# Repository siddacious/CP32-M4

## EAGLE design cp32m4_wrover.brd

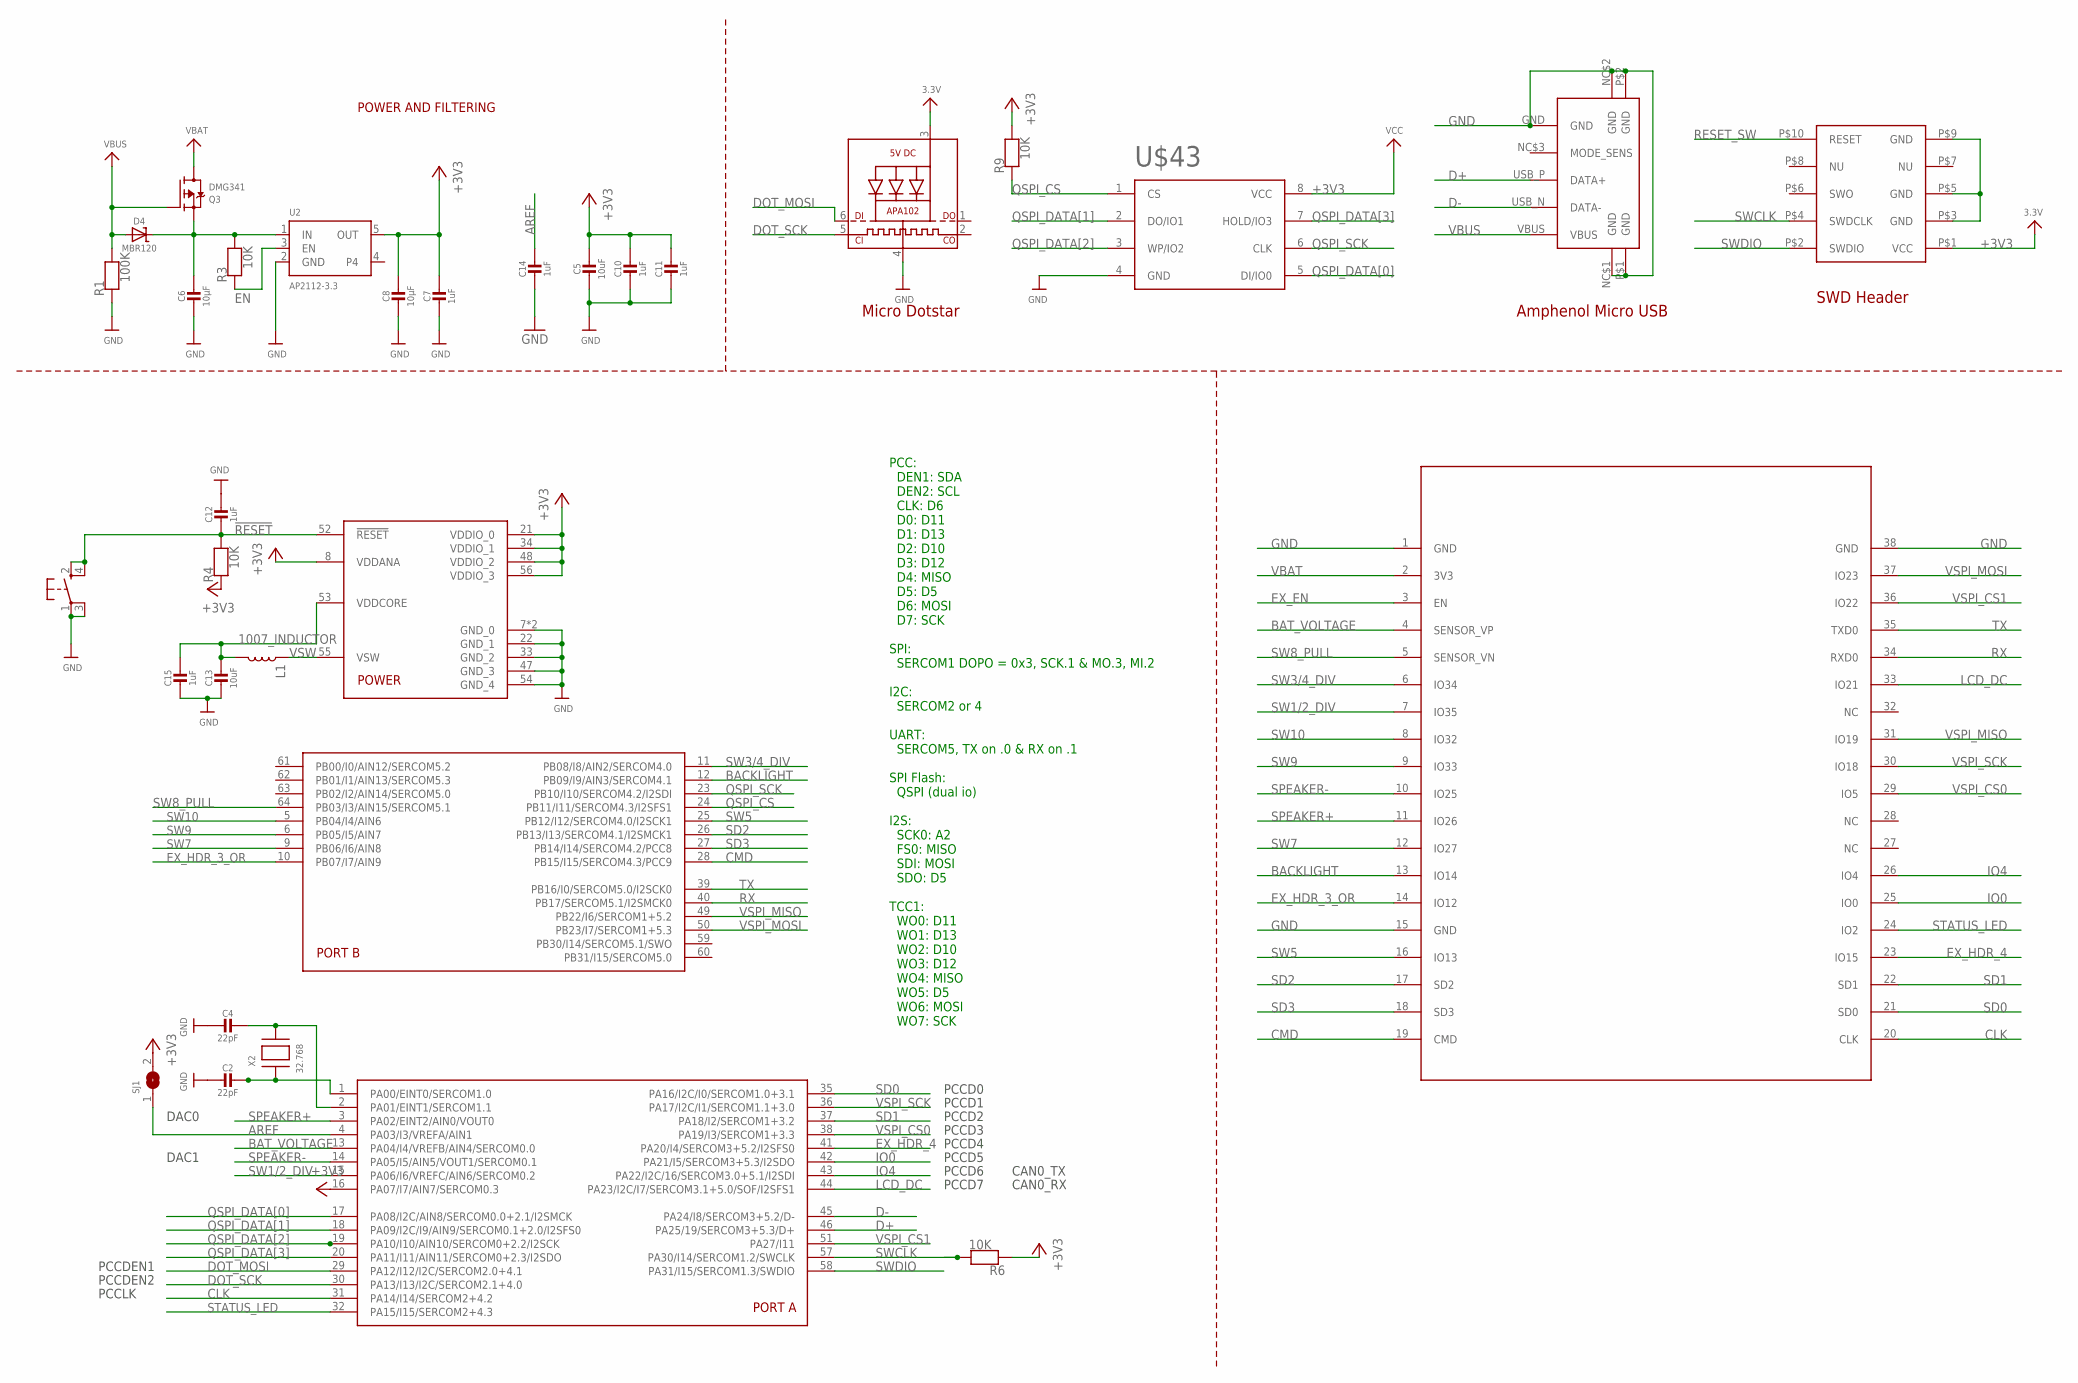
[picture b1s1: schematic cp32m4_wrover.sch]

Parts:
C2, C4: 22pF; 0603-NO
C5, C13: 10uF; 0805-NO
C6, C8: 10µF; 0805-NO
C7, C10, C11, C12, C14, C15: 1uF; 0603-NO
D4: MBR120; SOD-123
L1: 1007_INDUCTOR
LED2: AP102-2020; APA102_2020
Q3: DMG341; SOT23-R
R1: 100K; 0603-NO
R3, R4, R6, R9: 10K; 0603-NO
SJ1: SOLDERJUMPERCLOSED; SOLDERJUMPER_CLOSEDWIRE
SW1: SPST_TACT-KMR2; KMR2
U2: AP2112-3.3; SOT23-5
U$7: ESP32_WROVER
U$14: ATSAMD51J; PQFN64-1
U$43: WINDBOND_QSPI_FLASHWSON_6X5; WSON_6X5MM
U$44: SWD_HEADER; AMPHENOL_SWD
U$50: AMPHENOL_MICRO_USBAMPHENOL_MICRO_USB_BETTER; BETTER_AMP_MICRO_USB
X2: 32.768; XTAL3215

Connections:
!RESET: C12.2, R4.2, SW1.2 (S), SW1.4 (S1), U$14.52 (!RESET)
+3V3: C5.1, C7.1, C8.1, C10.1, C11.1, LED2.3 (VDD), R4.1, R6.1, R9.2, SJ1.2, U2.5 (OUT), U$14.8 (VDDANA), U$14.16 (PA07/I7/AIN7/SERCOM0.3), U$14.21 (VDDIO_0), U$14.34 (VDDIO_1), U$14.48 (VDDIO_2), U$14.56 (VDDIO_3), U$43.8 (VCC), U$44.P$1 (VCC)
AREF: C14.1, SJ1.1, U$14.4 (PA03/I3/VREFA/AIN1)
BACKLIGHT: U$7.13 (IO14), U$14.12 (PB09/I9/AIN3/SERCOM4.1)
BAT_VOLTAGE: U$7.4 (SENSOR_VP), U$14.13 (PA04/I4/VREFB/AIN4/SERCOM0.0)
CLK: U$7.20 (CLK), U$14.31 (PA14/I14/SERCOM2+4.2)
CMD: U$7.19 (CMD), U$14.28 (PB15/I15/SERCOM4.3/PCC9)
D+: U$14.46 (PA25/19/SERCOM3+5.3/D+), U$50.USB_P (DATA+)
D-: U$14.45 (PA24/I8/SERCOM3+5.2/D-), U$50.USB_N (DATA-)
DOT_MOSI: LED2.6 (DI), U$14.29 (PA12/I12/I2C/SERCOM2.0+4.1)
DOT_SCK: LED2.5 (CKI), U$14.30 (PA13/I13/I2C/SERCOM2.1+4.0)
EN: R3.1, U2.3 (EN)
EX_EN: U$7.3 (EN)
EX_HDR_3_OR: U$7.14 (IO12), U$14.10 (PB07/I7/AIN9)
EX_HDR_4: U$7.23 (IO15), U$14.41 (PA20/I4/SERCOM3+5.2/I2SFS0)
GND: C2.2, C4.2, C5.2, C6.2, C7.2, C8.2, C10.2, C11.2, C12.1, C13.2, C14.2, C15.2, LED2.4 (GND), R1.1, SW1.1, SW1.3 (P1), U2.2 (GND), U$7.1 (GND), U$7.15 (GND), U$7.38 (GND), U$14.7 (GND_0), U$14.22 (GND_1), U$14.33 (GND_2), U$14.47 (GND_3), U$14.54 (GND_4), U$14.EXP (GND_0), U$43.4 (GND), U$44.P$3 (GND), U$44.P$5 (GND), U$44.P$9 (GND), U$50.GND, U$50.NC$1 (GND), U$50.NC$2 (GND), U$50.P$1 (GND), U$50.P$2 (GND)
IO0: U$7.25 (IO0), U$14.42 (PA21/I5/SERCOM3+5.3/I2SDO)
IO4: U$7.26 (IO4), U$14.43 (PA22/I2C/16/SERCOM3.0+5.1/I2SDI)
LCD_DC: U$7.33 (IO21), U$14.44 (PA23/I2C/I7/SERCOM3.1+5.0/SOF/I2SFS1)
unnamed: C2.1, U$14.1 (PA00/EINT0/SERCOM1.0), X2.P$1
unnamed: C4.1, U$14.2 (PA01/EINT1/SERCOM1.1), X2.P$2
QSPI_CS: R9.1, U$14.24 (PB11/I11/SERCOM4.3/I2SFS1), U$43.1 (CS)
QSPI_DATA[0]: U$14.17 (PA08/I2C/AIN8/SERCOM0.0+2.1/I2SMCK), U$43.5 (DI/IO0)
QSPI_DATA[1]: U$14.18 (PA09/I2C/I9/AIN9/SERCOM0.1+2.0/I2SFS0), U$43.2 (DO/IO1)
QSPI_DATA[2]: U$14.19 (PA10/I10/AIN10/SERCOM0+2.2/I2SCK), U$43.3 (WP/IO2)
QSPI_DATA[3]: U$14.20 (PA11/I11/AIN11/SERCOM0+2.3/I2SDO), U$43.7 (HOLD/IO3)
QSPI_SCK: U$14.23 (PB10/I10/SERCOM4.2/I2SDI), U$43.6 (CLK)
RESET_SW: U$44.P$10 (RESET)
RX: U$7.34 (RXD0), U$14.40 (PB17/SERCOM5.1/I2SMCK0)
SD0: U$7.21 (SD0), U$14.35 (PA16/I2C/I0/SERCOM1.0+3.1)
SD1: U$7.22 (SD1), U$14.37 (PA18/I2/SERCOM1+3.2)
SD2: U$7.17 (SD2), U$14.26 (PB13/I13/SERCOM4.1/I2SMCK1)
SD3: U$7.18 (SD3), U$14.27 (PB14/I14/SERCOM4.2/PCC8)
SPEAKER+: U$7.11 (IO26), U$14.3 (PA02/EINT2/AIN0/VOUT0)
SPEAKER-: U$7.10 (IO25), U$14.14 (PA05/I5/AIN5/VOUT1/SERCOM0.1)
STATUS_LED: U$7.24 (IO2), U$14.32 (PA15/I15/SERCOM2+4.3)
SW1/2_DIV: U$7.7 (IO35), U$14.15 (PA06/I6/VREFC/AIN6/SERCOM0.2)
SW3/4_DIV: U$7.6 (IO34), U$14.11 (PB08/I8/AIN2/SERCOM4.0)
SW5: U$7.16 (IO13), U$14.25 (PB12/I12/SERCOM4.0/I2SCK1)
SW7: U$7.12 (IO27), U$14.9 (PB06/I6/AIN8)
SW8_PULL: U$7.5 (SENSOR_VN), U$14.64 (PB03/I3/AIN15/SERCOM5.1)
SW9: U$7.9 (IO33), U$14.6 (PB05/I5/AIN7)
SW10: U$7.8 (IO32), U$14.5 (PB04/I4/AIN6)
SWCLK: R6.2, U$14.57 (PA30/I14/SERCOM1.2/SWCLK), U$44.P$4 (SWDCLK)
SWDIO: U$14.58 (PA31/I15/SERCOM1.3/SWDIO), U$44.P$2 (SWDIO)
TX: U$7.35 (TXD0), U$14.39 (PB16/I0/SERCOM5.0/I2SCK0)
VBAT: Q3.3 (D), U$7.2 (3V3)
VBUS: D4.A, Q3.1 (G), R1.2, U$50.VBUS
VDDCORE1: C13.1, C15.1, L1.P$2 (2), U$14.53 (VDDCORE)
VHI: C6.1, D4.C, Q3.2 (S), R3.2, U2.1 (IN)
VSPI_CS0: U$7.29 (IO5), U$14.38 (PA19/I3/SERCOM1+3.3)
VSPI_CS1: U$7.36 (IO22), U$14.51 (PA27/I11)
VSPI_MISO: U$7.31 (IO19), U$14.49 (PB22/I6/SERCOM1+5.2)
VSPI_MOSI: U$7.37 (IO23), U$14.50 (PB23/I7/SERCOM1+5.3)
VSPI_SCK: U$7.30 (IO18), U$14.36 (PA17/I2C/I1/SERCOM1.1+3.0)
VSW: L1.P$1 (1), U$14.55 (VSW)

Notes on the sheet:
POWER AND FILTERING
PCCDEN1
PCCDEN2
PCCD0
PCCD1
PCCD2
PCCD3
PCCD4
PCCD5
PCCD6
PCCD7
PCCLK
PCC: DEN1: SDA DEN2: SCL CLK: D6 D0: D11 D1: D13 D2: D10 D3: D12 D4: MISO D5: D5 D6: MOSI D7: SCK SPI: SERCOM1 DOPO = 0x3, SCK.1 & MO.3, MI.2 I2C: SERCOM2 or 4 UART: SERCOM5, TX on .0 & RX on .1 SPI Flash: QSPI (dual io) I2S: SCK0: A2 FS0: MISO SDI: MOSI SDO: D5 TCC1: WO0: D11 WO1: D13 WO2: D10 WO3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
CAN0_TX
CAN0_RX
DAC0
DAC1
SWD Header
Micro Dotstar
Amphenol Micro USB

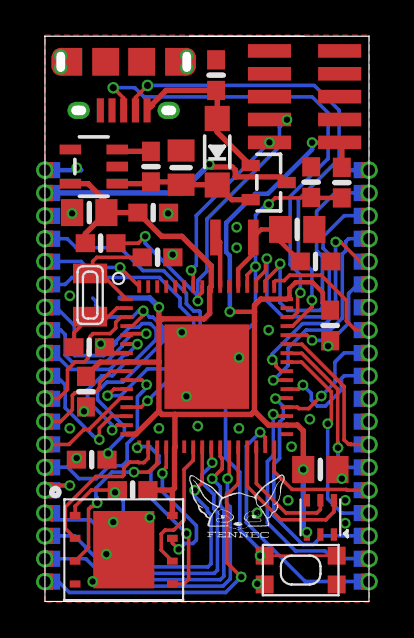
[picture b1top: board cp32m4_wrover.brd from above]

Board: 2 copper layers, 17.5 x 30.9 mm, 30 parts (1 on the bottom side), 54 nets.

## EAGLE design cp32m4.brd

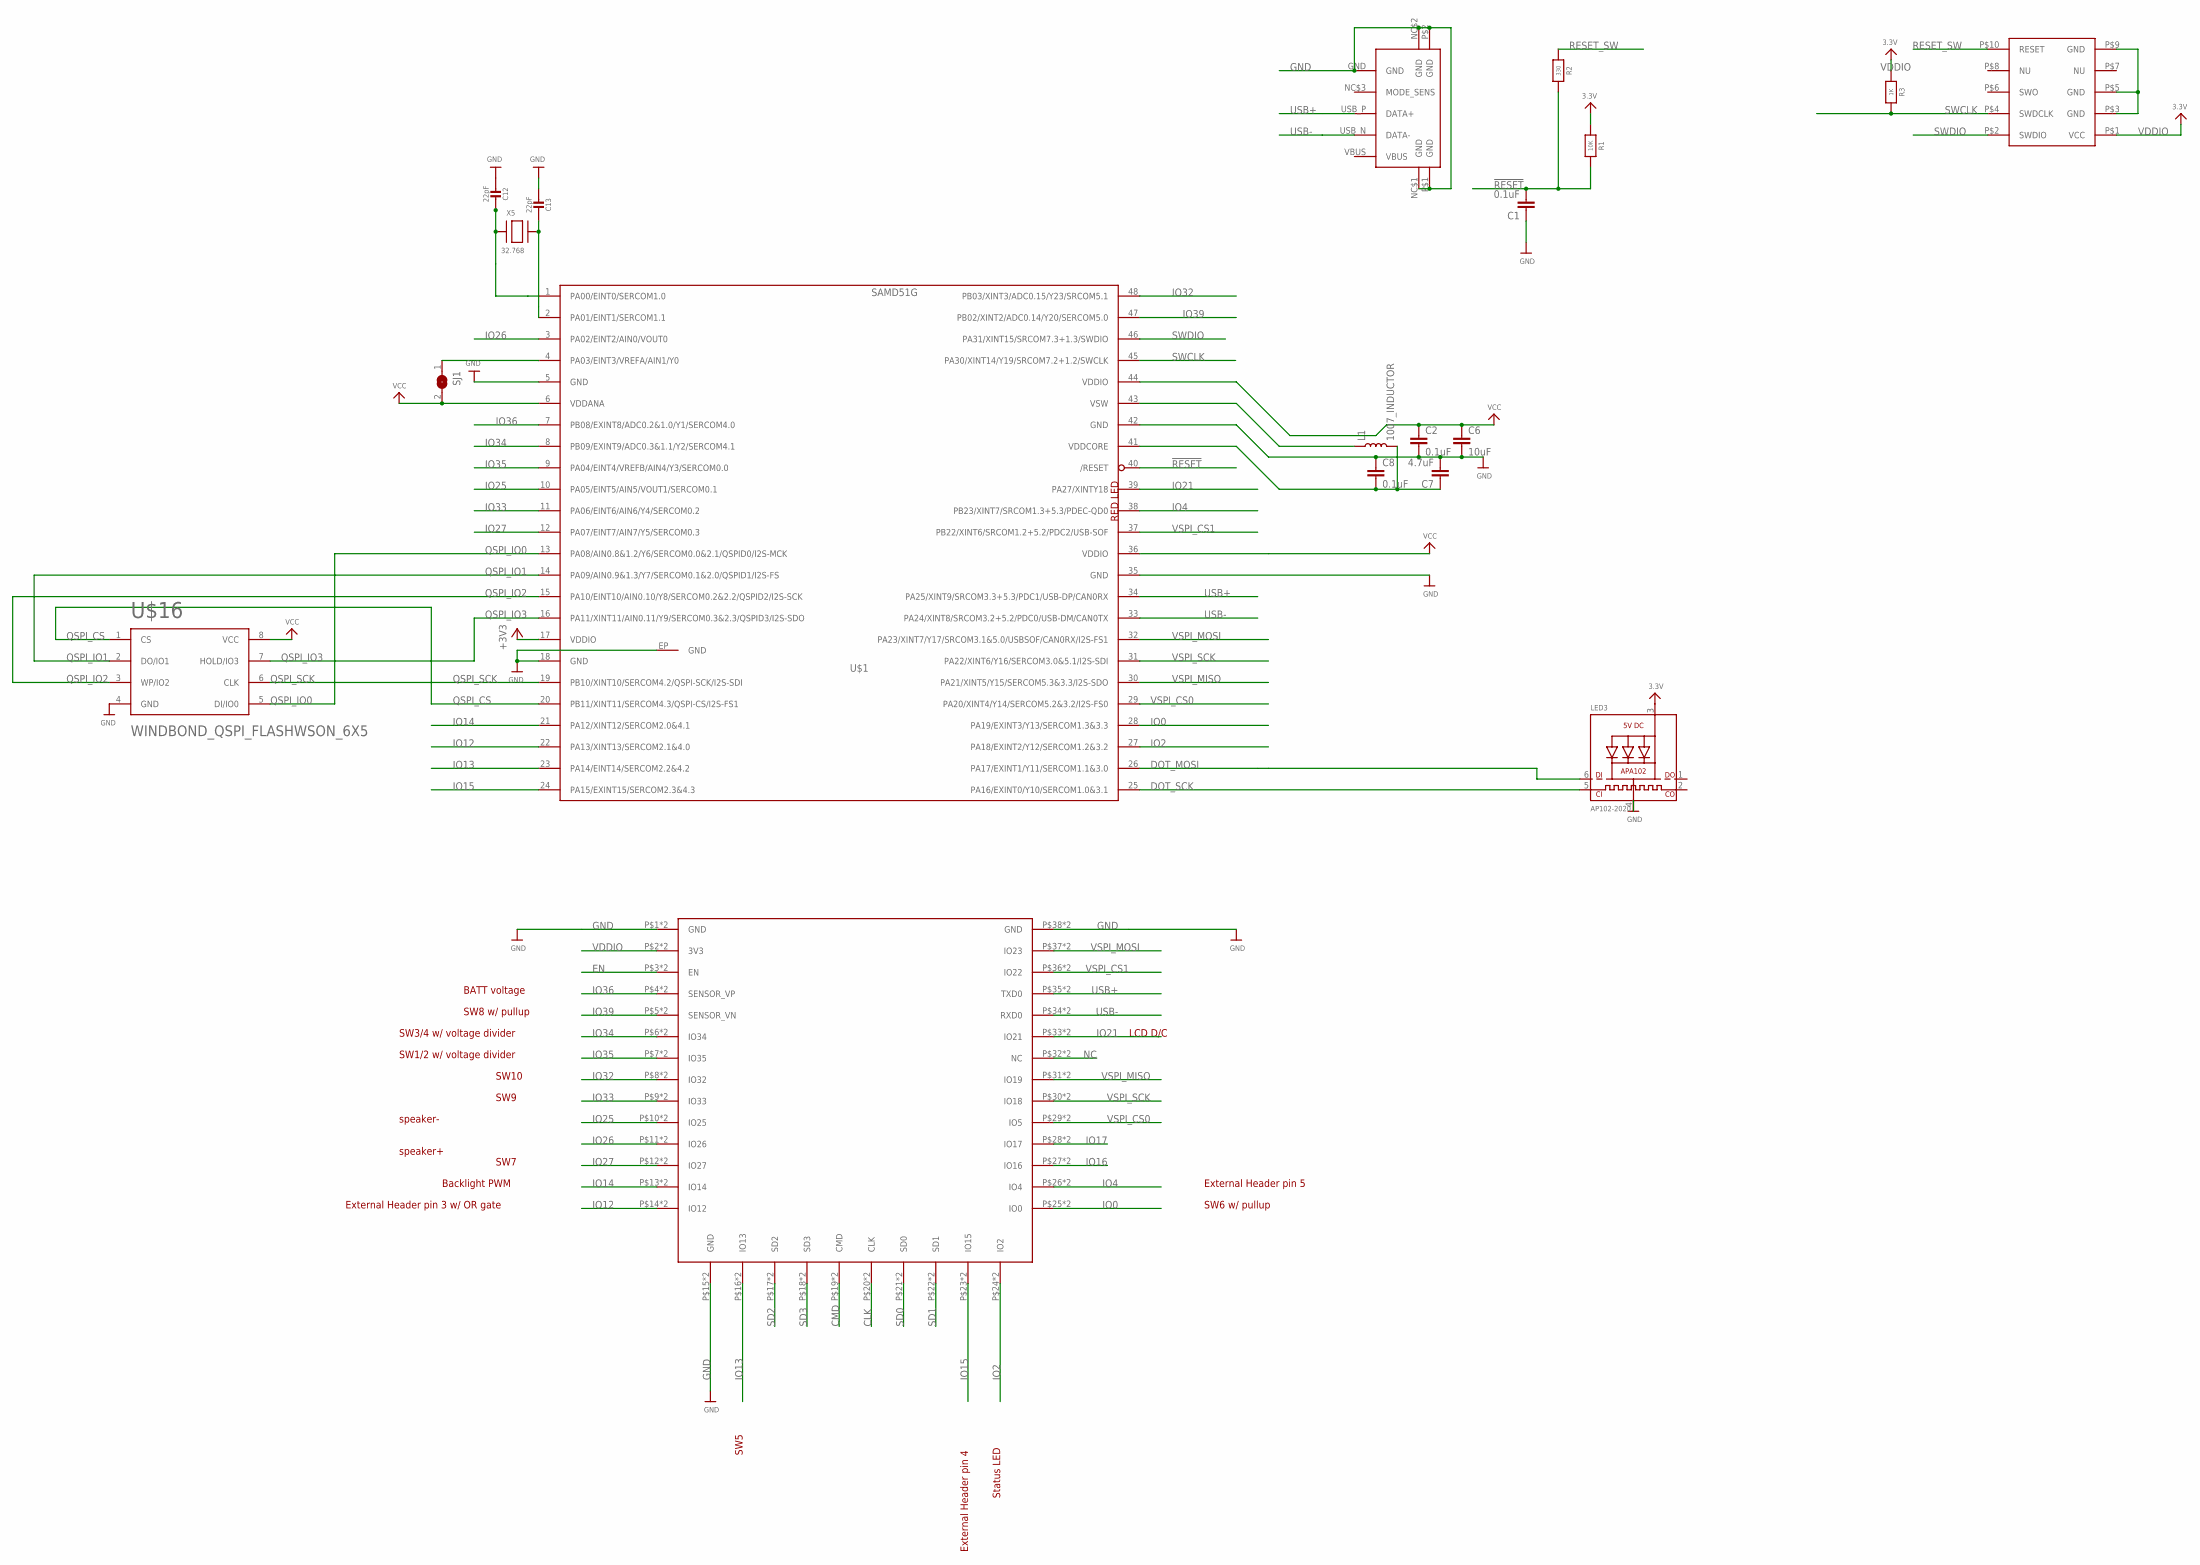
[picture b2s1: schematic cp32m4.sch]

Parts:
C1, C2, C8: 0.1uF; 0603
C6: 10uF; 0805
C7: 4.7uF; 0603
C12, C13: 22pF; 0603-NO
L1: 1007_INDUCTOR
LED3: AP102-2020; APA102_2020
R1: 10K; 0603-NO
R2: 330; 0603-NO
R3: 1K; 0603-NO
SJ1: SOLDERJUMPERCLOSED; SOLDERJUMPER_CLOSEDWIRE
U$1: SAMD51G; QFN-48
U$2: SWD_HEADER; AMPHENOL_SWD
U$5: WROOM; ESP32_WROOM
U$16: WINDBOND_QSPI_FLASHWSON_6X5; WSON_6X5MM
U$19: AMPHENOL_MICRO_USBAMPHENOL_MICRO_USB_BETTER; BETTER_AMP_MICRO_USB
X5: 32.768; XTAL3215

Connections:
!RESET: C1.2, R1.1, R2.1, U$1.40 (/RESET)
AREF: SJ1.1, U$1.4 (PA03/EINT3/VREFA/AIN1/Y0)
CLK: U$5.P$20 (CLK), U$5.PP$20 (CLK)
CMD: U$5.P$19 (CMD), U$5.PP$19 (CMD)
DOT_MOSI: LED3.6 (DI), U$1.26 (PA17/EXINT1/Y11/SERCOM1.1&3.0)
DOT_SCK: LED3.5 (CKI), U$1.25 (PA16/EXINT0/Y10/SERCOM1.0&3.1)
EN: U$5.P$3 (EN), U$5.PP$3 (EN)
GND: C1.1, C2.2, C6.2, C7.2, C8.1, C12.2, C13.2, LED3.4 (GND), U$1.5 (GND), U$1.18 (GND), U$1.35 (GND), U$1.42 (GND), U$1.EP (GND), U$2.P$3 (GND), U$2.P$5 (GND), U$2.P$9 (GND), U$5.P$1 (GND), U$5.P$15 (GND), U$5.P$38 (GND), U$5.PP$1 (GND), U$5.PP$15 (GND), U$5.PP$38 (GND), U$16.4 (GND), U$19.GND, U$19.NC$1 (GND), U$19.NC$2 (GND), U$19.P$1 (GND), U$19.P$2 (GND)
IO0: U$1.28 (PA19/EXINT3/Y13/SERCOM1.3&3.3), U$5.P$25 (IO0), U$5.PP$25 (IO0)
IO2: U$1.27 (PA18/EXINT2/Y12/SERCOM1.2&3.2), U$5.P$24 (IO2), U$5.PP$24 (IO2)
IO4: U$1.38 (PB23/XINT7/SRCOM1.3+5.3/PDEC-QD0), U$5.P$26 (IO4), U$5.PP$26 (IO4)
IO12: U$1.22 (PA13/XINT13/SERCOM2.1&4.0), U$5.P$14 (IO12), U$5.PP$14 (IO12)
IO13: U$1.23 (PA14/EINT14/SERCOM2.2&4.2), U$5.P$16 (IO13), U$5.PP$16 (IO13)
IO14: U$1.21 (PA12/XINT12/SERCOM2.0&4.1), U$5.P$13 (IO14), U$5.PP$13 (IO14)
IO15: U$1.24 (PA15/EXINT15/SERCOM2.3&4.3), U$5.P$23 (IO15), U$5.PP$23 (IO15)
IO16: U$5.P$27 (IO16), U$5.PP$27 (IO16)
IO17: U$5.P$28 (IO17), U$5.PP$28 (IO17)
IO21: U$1.39 (PA27/XINTY18), U$5.P$33 (IO21), U$5.PP$33 (IO21)
IO25: U$1.10 (PA05/EINT5/AIN5/VOUT1/SERCOM0.1), U$5.P$10 (IO25), U$5.PP$10 (IO25)
IO26: U$1.3 (PA02/EINT2/AIN0/VOUT0), U$5.P$11 (IO26), U$5.PP$11 (IO26)
IO27: U$1.12 (PA07/EINT7/AIN7/Y5/SERCOM0.3), U$5.P$12 (IO27), U$5.PP$12 (IO27)
IO32: U$1.48 (PB03/XINT3/ADC0.15/Y23/SRCOM5.1), U$5.P$8 (IO32), U$5.PP$8 (IO32)
IO33: U$1.11 (PA06/EINT6/AIN6/Y4/SERCOM0.2), U$5.P$9 (IO33), U$5.PP$9 (IO33)
IO34: U$1.8 (PB09/EXINT9/ADC0.3&1.1/Y2/SERCOM4.1), U$5.P$6 (IO34), U$5.PP$6 (IO34)
IO35: U$1.9 (PA04/EINT4/VREFB/AIN4/Y3/SERCOM0.0), U$5.P$7 (IO35), U$5.PP$7 (IO35)
IO36: U$1.7 (PB08/EXINT8/ADC0.2&1.0/Y1/SERCOM4.0), U$5.P$4 (SENSOR_VP), U$5.PP$4 (SENSOR_VP)
IO39: U$1.47 (PB02/XINT2/ADC0.14/Y20/SERCOM5.0), U$5.P$5 (SENSOR_VN), U$5.PP$5 (SENSOR_VN)
NC: U$5.P$32 (NC), U$5.PP$32 (NC)
QSPI_CS: U$1.20 (PB11/XINT11/SERCOM4.3/QSPI-CS/I2S-FS1), U$16.1 (CS)
QSPI_IO0: U$1.13 (PA08/AIN0.8&1.2/Y6/SERCOM0.0&2.1/QSPID0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), U$16.5 (DI/IO0)
QSPI_IO1: U$1.14 (PA09/AIN0.9&1.3/Y7/SERCOM0.1&2.0/QSPID1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), U$16.2 (DO/IO1)
QSPI_IO2: U$1.15 (PA10/EINT10/AIN0.10/Y8/SERCOM0.2&2.2/QS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), U$16.3 (WP/IO2)
QSPI_IO3: U$1.16 (PA11/XINT11/AIN0.11/Y9/SERCOM0.3&2.3/QS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), U$16.7 (HOLD/IO3)
QSPI_SCK: U$1.19 (PB10/XINT10/SERCOM4.2/QSPI-SCK/I2S-SDI), U$16.6 (CLK)
RESET_SW: R2.2, U$2.P$10 (RESET)
SD0: U$5.P$21 (SD0), U$5.PP$21 (SD0)
SD1: U$5.P$22 (SD1), U$5.PP$22 (SD1)
SD2: U$5.P$17 (SD2), U$5.PP$17 (SD2)
SD3: U$5.P$18 (SD3), U$5.PP$18 (SD3)
SWCLK: R3.1, U$1.45 (PA30/XINT14/Y19/SRCOM7.2+1.2/SWCLK), U$2.P$4 (SWDCLK)
SWDIO: U$1.46 (PA31/XINT15/SRCOM7.3+1.3/SWDIO), U$2.P$2 (SWDIO)
USB+: U$1.34 (PA25/XINT9/SRCOM3.3+5.3/PDC1/USB-DP/CAN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), U$5.P$35 (TXD0), U$5.PP$35 (TXD0), U$19.USB_P (DATA+)
USB-: U$1.33 (PA24/XINT8/SRCOM3.2+5.2/PDC0/USB-DM/CAN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), U$5.P$34 (RXD0), U$5.PP$34 (RXD0), U$19.USB_N (DATA-)
VDDCORE: C7.1, C8.2, L1.P$2 (2), U$1.41 (VDDCORE)
VDDIO: C2.1, C6.1, LED3.3 (VDD), R1.2, R3.2, SJ1.2, U$1.6 (VDDANA), U$1.17 (VDDIO), U$1.36 (VDDIO), U$1.44 (VDDIO), U$2.P$1 (VCC), U$5.P$2 (3V3), U$5.PP$2 (3V3), U$16.8 (VCC)
VSPI_CS0: U$1.29 (PA20/XINT4/Y14/SERCOM5.2&3.2/I2S-FS0), U$5.P$29 (IO5), U$5.PP$29 (IO5)
VSPI_CS1: U$1.37 (PB22/XINT6/SRCOM1.2+5.2/PDC2/USB-SOF), U$5.P$36 (IO22), U$5.PP$36 (IO22)
VSPI_MISO: U$1.30 (PA21/XINT5/Y15/SERCOM5.3&3.3/I2S-SDO), U$5.P$31 (IO19), U$5.PP$31 (IO19)
VSPI_MOSI: U$1.32 (PA23/XINT7/Y17/SRCOM3.1&5.0/USBSOF/CAN0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), U$5.P$37 (IO23), U$5.PP$37 (IO23)
VSPI_SCK: U$1.31 (PA22/XINT6/Y16/SERCOM3.0&5.1/I2S-SDI), U$5.P$30 (IO18), U$5.PP$30 (IO18)
VSW: L1.P$1 (1), U$1.43 (VSW)
XOSC32_A: C12.1, U$1.1 (PA00/EINT0/SERCOM1.0), X5.P$1
XOSC32_B: C13.1, U$1.2 (PA01/EINT1/SERCOM1.1), X5.P$2

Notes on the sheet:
RED LED
speaker-
speaker+
SW3/4 w/ voltage divider
SW1/2 w/ voltage divider
SW9
SW10
SW7
SW5
SW6 w/ pullup
Status LED
Backlight PWM
BATT voltage
External Header pin 4
External Header pin 5
LCD D/C
SW8 w/ pullup
External Header pin 3 w/ OR gate

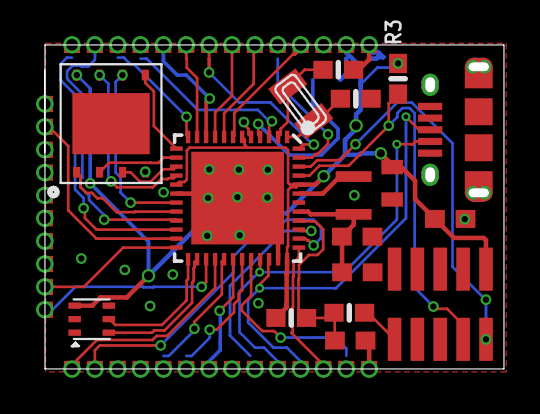
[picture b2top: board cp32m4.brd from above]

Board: 2 copper layers, 25.0 x 17.5 mm, 19 parts (1 on the bottom side), 53 nets.

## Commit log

2018-09-14 first draft
2018-09-14 added SWD and USB headers :|
2018-09-20 fully routed?
2018-09-20 touched up bottom silk
2018-10-26 mk1 fabbed
2018-12-16 rename an updates
2019-02-03 all pins netted for CP-32M4-WROVER
2019-02-03 routing done-ish, ground airwires
2019-02-04 major airwires fixed?
2019-02-05 all DRCs resolved
2019-02-05 as ordered from OSH Park #uC4aBCaJ

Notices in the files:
parts and their libraries:
SparkFun-Capacitors: Licensing: Creative Commons ShareAlike 4.0 International - https://creativecommons.org/licenses/by-sa/4.0
microbuilder: This work is placed in the public domain, and may be freely used for commercial and non-commercial work with the following conditions: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
